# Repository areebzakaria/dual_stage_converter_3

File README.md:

# Dual-Stage Buck Converter (44V to 12V & 5V)

This project features a high-efficiency dual-stage DC-DC buck converter designed using the **Texas Instruments LMR36506 synchronous regulator**.  
The board is optimized for a compact **40mm x 40mm footprint**, focusing on robust thermal management and EMI shielding.

---

## Technical Specifications
- **Input Voltage:** 44V DC (Nominal)  
- **Stage 1 Output:** 12V DC @ 600mA  
- **Stage 2 Output:** 5V DC @ 600mA (cascaded from 12V rail)  
- **Regulator IC:** LMR36506 (RPE Package - 9-Pin VQFN)  
- **Switching Frequency:** High frequency for reduced inductor size  

---

## Hardware Features

### 1. Thermal Management
Since the Stage 1 regulator drops a significant voltage (44V → 12V), heat dissipation is critical.
- **Thermal Vias:** An array of 0.25mm vias is placed directly on the IC's center thermal pad (Pin 9) to conduct heat to the bottom layer.  
- **Ground Plane:** A solid copper pour on the bottom layer acts as a primary heat sink and EMI shield.  

### 2. PCB Layout Optimization
- **Compact Footprint:** Entire design fits within a 40mm × 40mm area.  
- **High-Voltage Safety:** Optimized trace clearances (0.2mm) to handle the 44V input safely.  
- **Power Flow:** Linear layout from left (Input) to right (Output) with thick 0.8mm–1.0mm power traces.  
- **Connectors:** Standard 2.54mm pitch headers for easy lab probing and integration.  

---

## Project Goals
- Deliver a compact, efficient dual-stage buck converter for high-voltage input applications.  
- Ensure robust thermal management and EMI shielding for reliable operation.  
- Provide a lab-friendly design with standard connectors and safe clearances.  

---

## License
This project is released under the MIT License. See [LICENSE](LICENSE) for details.

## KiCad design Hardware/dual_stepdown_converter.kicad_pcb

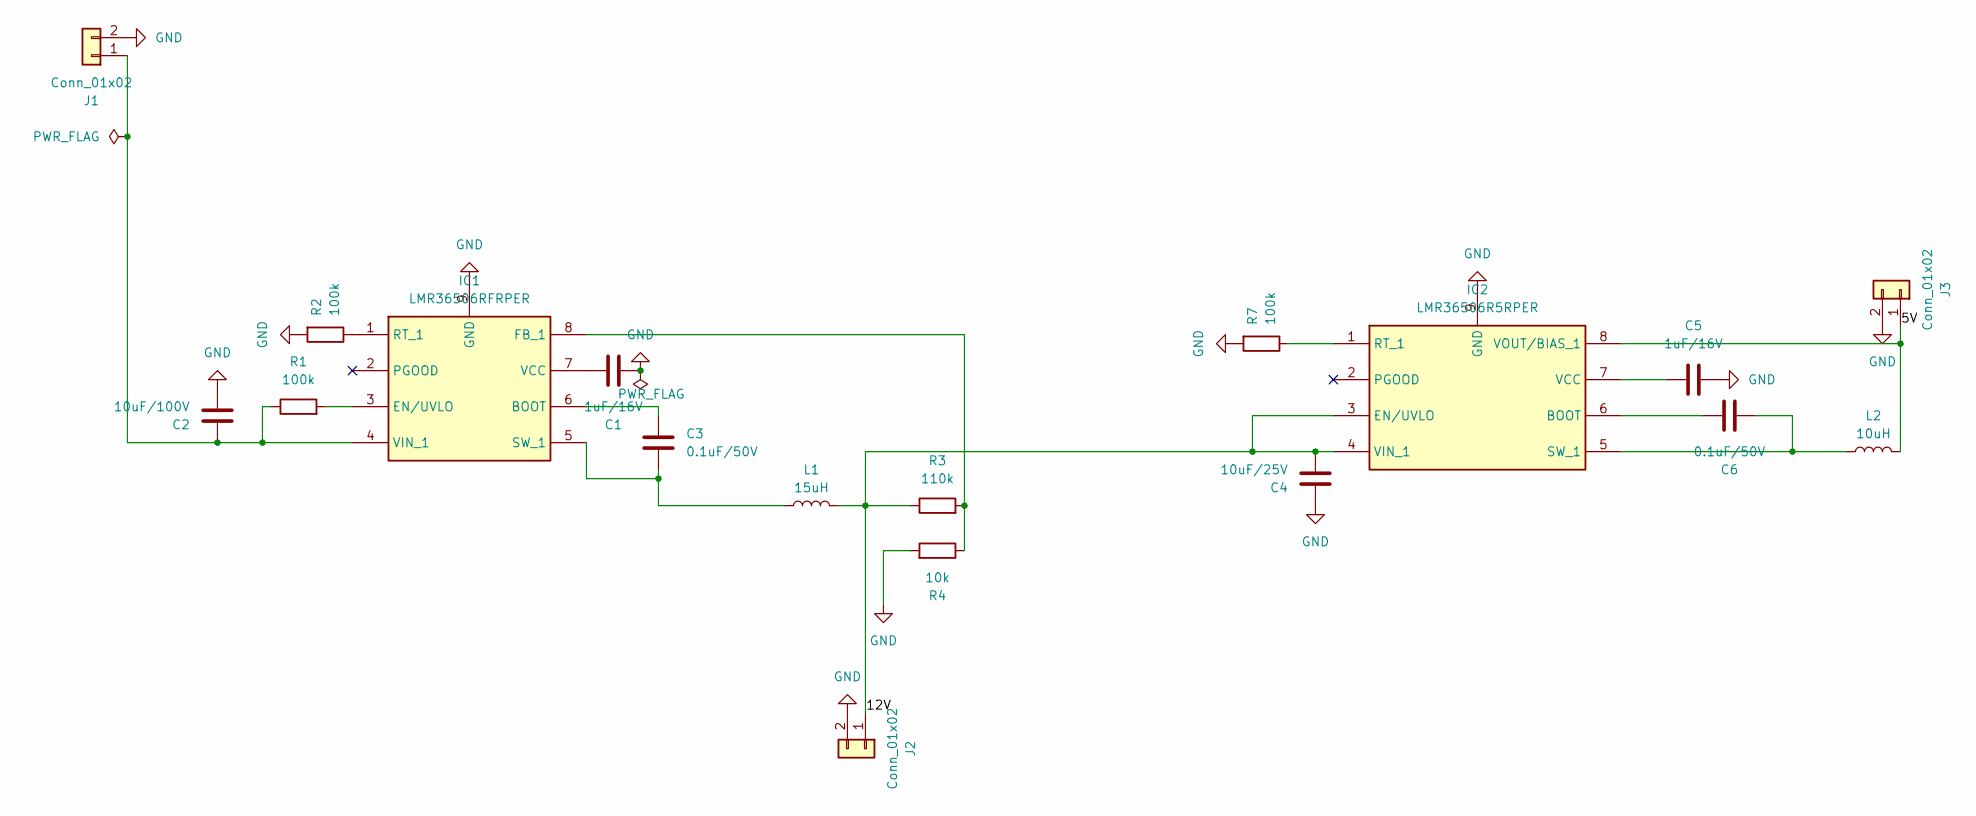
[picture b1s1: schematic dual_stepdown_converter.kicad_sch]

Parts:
C1, C5: 1uF/16V; C_0603_1608Metric
C2: 10uF/100V; C_1210_3225Metric
C3, C6: 0.1uF/50V; C_0603_1608Metric
C4: 10uF/25V; C_0805_2012Metric
IC1: LMR36506RFRPER; CONV_LMR36503MSC5RPERQ1; Mouser Part Number 595-LMR36506RFRPER
IC2: LMR36506R5RPER; CONV_LMR36503MSC5RPERQ1; Mouser Part Number 595-LMR36506R5RPER
J1, J2, J3: Conn_01x02; PinHeader_1x02_P2.54mm_Vertical
L1: 15uH; L_6.3x6.3_H3
L2: 10uH; L_6.3x6.3_H3
R1, R2, R7: 100k; R_0603_1608Metric
R3: 110k; R_0805_2012Metric
R4: 10k; R_0805_2012Metric

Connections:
/5V: IC2.8 (VOUT/BIAS_1), J3.1, L2.2
/12V: C4.2, IC2.3 (EN/UVLO), IC2.4 (VIN_1), J2.1, L1.2, R3.1
GND: C1.1, C2.2, C4.1, C5.1, IC1.9 (GND), IC2.9 (GND), J1.2, J2.2, J3.2, R2.2, R4.2, R7.2
unnamed: C3.2, IC1.6 (BOOT)
unnamed: IC1.3 (EN/UVLO), R1.2
unnamed: IC1.8 (FB_1), R3.2, R4.1
unnamed: IC1.1 (RT_1), R2.1
unnamed: C3.1, IC1.5 (SW_1), L1.1
unnamed: C1.2, IC1.7 (VCC)
unnamed: C2.1, IC1.4 (VIN_1), J1.1, R1.1
unnamed: C6.1, IC2.6 (BOOT)
unnamed: IC2.1 (RT_1), R7.1
unnamed: C6.2, IC2.5 (SW_1), L2.1
unnamed: C5.2, IC2.7 (VCC)

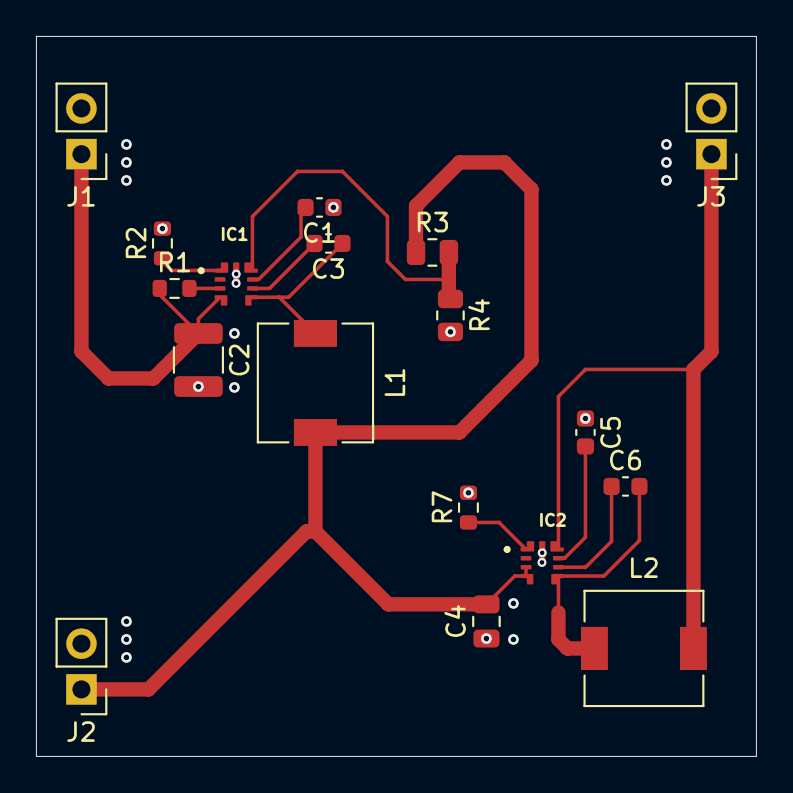
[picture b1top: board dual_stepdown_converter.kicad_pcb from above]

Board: 2 copper layers, 40.0 x 40.0 mm, 18 parts (0 on the bottom side), 14 nets.

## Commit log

2025-12-19 Create temp1
2025-12-19 Create temp2
